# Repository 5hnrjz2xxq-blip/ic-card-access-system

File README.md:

# IC卡门禁系统设计

数字信号处理课程 · 电子系统设计实训

## 项目简介

基于单片机的 IC 卡门禁系统课设：读卡 → 鉴权 → 控门 → 提示/记录；  
门边**旁置演示**（不动家里原锁），并扩展 **Home App 开锁** 与 **手机 NFC 自动化开锁**。

## 技术选型（方案 A 已定稿）

| 模块 | 方案 |
|------|------|
| 主控 | **ESP32-WROOM-32E**（自制 PCB 模组上板） |
| 读卡 | **MFRC522** 实体 Mifare 卡 + **PN532** 读手机 NFC |
| 显示 | OLED I2C（SSD1306） |
| 执行 | 继电器模拟门锁（旁置，不接原锁） |
| 供电 | Type-C 充电 + 3.7V 锂电 + 3.3V LDO |
| 无线 | WiFi + BLE（模组自带） |
| HomeKit | 软件 HAP，家庭 App 门锁开锁（**非** MFi Home Key） |
| iPhone | Home App 开锁 + 碰墙贴 NFC → **快捷指令**开锁 |
| 安卓 / 鸿蒙 | **手机当 IC 卡被 PN532 直接刷开**（HCE），**不是**碰贴触发命令 |
| 开发环境 | VS Code + PlatformIO（**macOS** 编译烧录监视均可用） |
| 代码托管 | GitHub Public |

不用作 HomeKit 主控：正点原子 ATK-T5（涂鸦生态）。

### 开锁通道一览

| 通道 | 说明 |
|------|------|
| 实体 IC 卡 | MFRC522 白名单（课设基础/提高） |
| iPhone · Home App | 软件 HomeKit 门锁 |
| iPhone · NFC | 碰墙贴 → 快捷指令（**非**原生 Home Key） |
| 安卓 / 鸿蒙 · NFC | **手机模拟卡 → PN532 直读开锁**（如刷 IC 卡） |
| 原生 Apple Home Key | **超范围**，需 MFi，课设不做 |

详细需求见 [`docs/需求说明.md`](docs/需求说明.md)，物料见 [`docs/元器件清单.md`](docs/元器件清单.md)。

交互方案应用（手机可打开）：[`index.html`](index.html)

## 开发环境（Windows / Mac）

本仓库在 **Windows 与 Mac** 之间切换开发，工具链统一为 VS Code + PlatformIO。

### 通用步骤

1. 安装 [VS Code](https://code.visualstudio.com/) 与 PlatformIO 插件
2. 安装并登录 GitHub CLI：`gh auth login`（协议选 HTTPS）
3. 同步代码：

```bash
git clone <本仓库地址>
cd <仓库目录>
```

4. 编译：

```bash
pio run
```

5. 烧录 / 监视（端口因机器而异，勿写死进仓库）：

```bash
pio run -t upload
pio device monitor
```

### 协作约定

- 开工先 `git pull`
- 改完 `commit` 后 `push`
- `upload_port` / `monitor_port` 各机器本地处理，不提交
- 仓库默认 **Public**

### 端口差异

| 系统 | 串口示例 |
|------|----------|
| Windows | `COM3` |
| macOS | `/dev/cu.usbmodem*` / `/dev/cu.usbserial*` |

## 目录结构

```text
├── README.md
├── index.html        # 方案 A 交互应用（手机预览）
├── platformio.ini    # PlatformIO 工程配置
├── .gitignore
├── .gitattributes
├── src/              # 固件源码（PlatformIO）
├── include/          # 头文件
├── docs/             # 需求、BOM、计划、原理图说明
├── hardware/         # 原理图 / PCB（KiCad、Gerber、DRC）
├── fab/              # 打样生产文件（Gerber / BOM / 坐标）
└── assets/           # 文档配图
```

## 开发进度

| 阶段 | 内容 | 状态 |
|------|------|------|
| 0 | 环境与仓库 | 进行中 |
| 1 | 需求与方案（方案 A + BOM） | **完成** |
| 2 | 读卡模块联调 | 未开始 |
| 3 | 白名单鉴权与控门 | 未开始 |
| 4 | 管理与记录 | 未开始 |
| 5 | HomeKit / NFC 自动化 | 未开始 |
| 6 | 文档与答辩 | 未开始 |

## 组员

（待补充）

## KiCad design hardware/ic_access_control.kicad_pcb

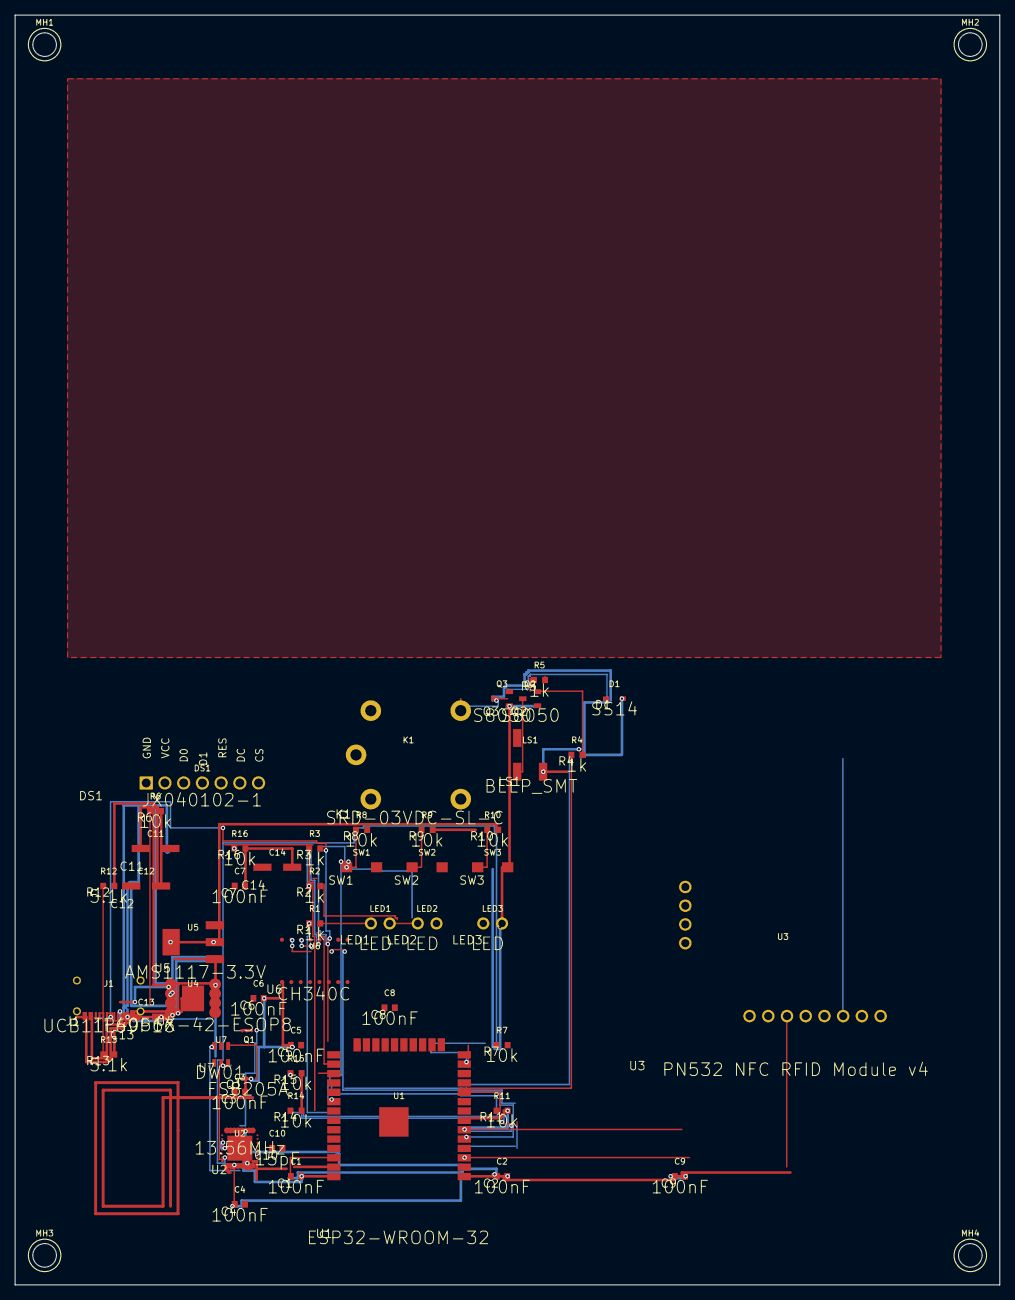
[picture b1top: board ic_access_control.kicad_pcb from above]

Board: 2 copper layers, 133.5 x 172.2 mm, 55 parts (0 on the bottom side), 44 nets.

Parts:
C1, C2, C3, C4, C5, C6, C7, C8, C9, C10: C0603
C11, C12, C13, C14: CAP-SMD_BD4.0-L4.3-W4.3-LS5.3-FD
D1: SOD-323_L1.7-W1.3-LS2.6-RD-1
DS1: OLED-TH_JX040101-1
J1: TYPE-C-SMD_16P-UCB11L69P16
K1: RELAY-TH_SRD-XXVDC-XL-C
LED1, LED2, LED3: LED-TH_BD4.0-P2.54-FD_RED
LS1: BUZ-SMD_3P-L5.2-W5.2-P3.50-BR
MH1, MH2, MH3, MH4: MountingHole_3.2mm_M3
Q1: TSSOP-8_L4.4-W3.0-P0.65-LS6.4-BL-2
Q2, Q3: SOT-23-3_L2.9-W1.3-P1.90-LS2.4-BR
R1, R2, R3, R4, R5, R6, R7, R8, R9, R10, R11, R12, R13, R14, R15, R16: R0603
SW1, SW2, SW3: SW-SMD_L4.0-W2.9-LS5.0
U1: WIFIM-SMD_ESP-WROOM-32
U2: QFN-32_L5.0-W5.0-P0.50-BL-EP3.4
U3: COMM-TH_L42.7-W40.4_PN532_NFC_RFID
U4: SOP-8_L4.9-W3.9-P1.27-LS6.0-TL-EP
U5: SOT-223-3_L6.5-W3.4-P2.30-LS7.0-BR
U6: SOP-16_L10.0-W3.9-P1.27-LS6.0-BL
U7: SOT-23-6_L2.9-W1.6-P0.95-LS2.8-BL

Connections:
+3V3: C2.1, C3.1, C5.1, C8.1, C9.1, C13.1, C14.1, D1.2, K1.1, LS1.1, R7.2, R8.2, R9.2, R10.2, R11.2, R14.2, R15.2, U1.2, U2.6, U2.16, U2.17, U2.19, U3.1, U5.2, U5.4, U6.16
ANT1: C10.2, U2.5, U2.8
ANT_RX: C10.1, U2.23
BAT_GND: Q1.1, Q1.2, Q1.3, U7.6
BOOT: R11.1, U1.25
BUZ: R4.1, U1.10
BUZ_C: LS1.2, Q2.3
CC1: J1.A5, R12.1
CC2: J1.B5, R13.1
CH_V3: C7.1, U6.4
EN: C1.1, R7.1, U1.3
GND: C1.2, C2.2, C3.2, C4.2, C5.2, C6.2, C7.2, C8.2, C9.2, C11.2, C12.2, C13.2, C14.2, J1.1, J1.A1, J1.A12, J1.B1, J1.B12, LED1.2, LED2.2, LED3.2, Q1.6, Q1.7, Q1.8, Q2.2, Q3.2, R6.2, R12.2, R13.2, R16.2, SW1.2, SW2.2, SW3.2, U1.1, U1.15, U1.38, U1.39, U2.7, U2.18, U2.22, U2.30, U2.32, U2.33, U3.2, U3.10, U4.3, U4.9, U5.1, U6.1
LED_G: R1.1, U1.11
LED_R: R2.1, U1.12
LED_S: R3.1, U1.8
NLED1: LED1.1, R1.2
NLED2: LED2.1, R2.2
NLED3: LED3.1, R3.2
NQB2: Q2.1, R4.2
NQB3: Q3.1, R5.2
OC: Q1.5, U7.3
OD: Q1.4, U7.1
PN_SS: U1.23, U3.6
PROG: R6.1, U4.2
RC_RST: U1.13, U2.25
RC_SS: U1.29, U2.29
RLY: R5.1, U1.28
RLY_C: D1.1, K1.2, Q3.3
SCL: R15.1, U1.36, U3.12
SDA: R14.1, U1.33, U3.11
SPI_MISO: U1.31, U2.26, U3.4
SPI_MOSI: U1.37, U2.27, U3.3
SPI_SCK: U1.30, U2.28, U3.5
SW1: R8.1, SW1.1, U1.9
SW2: R9.1, SW2.1, U1.26
SW3: R10.1, SW3.1, U1.16
TEMP: R16.1, U4.1
UART_RX: U1.34, U6.3
UART_TX: U1.35, U6.2
USB_DN: J1.A7, J1.B7, U6.6
USB_DP: J1.A6, J1.B6, U6.5
VBAT: C12.1, U4.5, U5.3, U7.5
VBUS: C6.1, C11.1, J1.A4, J1.A9, J1.B4, J1.B9, U4.4
VMID: C4.1, U2.24

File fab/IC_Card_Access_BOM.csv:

No.	Quantity	Comment	Designator	Footprint	Value	Manufacturer Part	Manufacturer	Supplier Part	Supplier
1	9	100nF	C1,C2,C3,C4,C5,C6,C7,C8,C9	C0603	100nF	ST18B104K500CT	Walsin(华新科)	C2918557	LCSC
2	1	15pF	C10	C0603	15pF	ST18B104K500CT	Walsin(华新科)		LCSC
3	4	CAP-SMD 4*5 10uF ±10% 16V	C11,C12,C13,C14	CAP-SMD_BD4.0-L4.3-W4.3-LS5.3-FD	10uF	CAP-SMD 4*5 10uF ±10% 16V		C9900020910	LCSC
4	1	SS14	D1	SOD-323_L1.7-W1.3-LS2.6-RD-1		SS14		C9900013398	LCSC
5	1	JX040102-1	DS1	OLED-TH_JX040101-1		JX040102-1	技小新	C284855	LCSC
6	1	UCB11L69P16	J1	TYPE-C-SMD_16P-UCB11L69P16		UCB11L69P16		C9900009190	LCSC
7	1	SRD-03VDC-SL-C	K1	RELAY-TH_SRD-XXVDC-XL-C		SRD-03VDC-SL-C	松乐	C24585	LCSC
8	3	LED	LED1,LED2,LED3	LED-TH_BD4.0-P2.54-FD_RED		LED		C9900015665	LCSC
9	1	BEEP_SMT	LS1	BUZ-SMD_3P-L5.2-W5.2-P3.50-BR		BEEP_SMT		C9900006792	LCSC
10	1	FS8205A	Q1	TSSOP-8_L4.4-W3.0-P0.65-LS6.4-BL-2		FS8205A		C14212	LCSC
11	2	S8050	Q2,Q3	SOT-23-3_L2.9-W1.3-P1.90-LS2.4-BR		S8050	Doeshare(德芯)	C2931719	LCSC
12	5	1k	R1,R2,R3,R4,R5	R0603	1k				
13	9	10k	R6,R7,R8,R9,R10,R11,R14,R15,R16	R0603	10k				
14	2	5.1k	R12,R13	R0603	5.1k	RMC06035.1K1%N	Tyohm(幸亚电阻)		LCSC
15	3	轻触按键3*4*H	SW1,SW2,SW3	SW-SMD_L4.0-W2.9-LS5.0		轻触按键3*4*H		C9900017573	LCSC
16	1	ESP32-WROOM-32	U1	WIFIM-SMD_ESP-WROOM-32		ESP32-WROOM-32		C95209	LCSC
17	1	13.56MHz	U2	QFN-32_L5.0-W5.0-P0.50-BL-EP3.4	13.56MHz	MFRC52202HN1,151	NXP(恩智浦)	C11322	LCSC
18	1	PN532 NFC RFID Module v4	U3	COMM-TH_L42.7-W40.4_PN532_NFC_RFID		PN532 NFC RFID Module v4		C9900233104	LCSC
19	1	TP4056X-42-ESOP8	U4	SOP-8_L4.9-W3.9-P1.27-LS6.0-TL-EP		TP4056X-42-ESOP8	TOPPOWER(南京拓微)	C2763448	LCSC
20	1	AMS1117-3.3V	U5	SOT-223-3_L6.5-W3.4-P2.30-LS7.0-BR		AMS1117-3.3V	JSMSEMI(杰盛微)	C5205141	LCSC
21	1	CH340C	U6	SOP-16_L10.0-W3.9-P1.27-LS6.0-BL		CH340C	WCH(南京沁恒)	C84681	LCSC
22	1	DW01	U7	SOT-23-6_L2.9-W1.6-P0.95-LS2.8-BL		DW01	Slkor(萨科微)	C359989	LCSC

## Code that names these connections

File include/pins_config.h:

#pragma once

#include <Arduino.h>

// ==========================================
// IC 卡门禁系统 · 硬件引脚分配
// 对齐 docs/PCB原理图连线规格.md
// ==========================================

// SPI 总线（MFRC522 与 PN532 共用）
constexpr int8_t PIN_SPI_SCK  = 18;
constexpr int8_t PIN_SPI_MISO = 19;
constexpr int8_t PIN_SPI_MOSI = 23;

// MFRC522 (实体 Mifare 卡读头)
constexpr int8_t PIN_RC_SS    = 5;
constexpr int8_t PIN_RC_RST   = 14;

// PN532 (手机 HCE 虚拟卡读头)
constexpr int8_t PIN_PN_SS    = 15;

// I2C 总线 (0.96" OLED SSD1306)
constexpr int8_t PIN_I2C_SDA  = 21;
constexpr int8_t PIN_I2C_SCL  = 22;
constexpr uint8_t OLED_I2C_ADDR = 0x3C;

// 声光交互
constexpr int8_t PIN_BUZZER   = 25;  // Q2 驱动高电平鸣响
constexpr int8_t PIN_LED_G    = 26;  // 绿色 LED：通过
constexpr int8_t PIN_LED_R    = 27;  // 红色 LED：拒绝/报警
constexpr int8_t PIN_LED_S    = 32;  // 蓝色/状态 LED

// 门锁执行机构
constexpr int8_t PIN_RELAY    = 17;  // Q3 驱动高电平吸合
constexpr int8_t PIN_SERVO    = 16;  // 舵机 PWM 信号线 (SG90 橙线)
constexpr int    SERVO_LOCKED_ANGLE   = 0;   // 闭锁角度
constexpr int    SERVO_UNLOCKED_ANGLE = 90;  // 开锁角度

// 人机按键（按下接地，内部/外部上拉）
constexpr int8_t PIN_SW_ADMIN = 33;  // SW1 管理模式
constexpr int8_t PIN_SW_ADD   = 4;   // SW2 录入白名单
constexpr int8_t PIN_SW_DEL   = 13;  // SW3 删除/确认

// 时间参数配置（毫秒）
constexpr uint32_t DOOR_UNLOCK_DURATION_MS = 3000; // 开门持续 3 秒后自动闭锁
constexpr uint32_t CARD_REPEAT_INTERVAL_MS = 2500; // 同一张卡刷卡防重读间隔 2.5 秒
constexpr size_t   MAX_WHITELIST_CAPACITY  = 30;   // 白名单最大容量
constexpr size_t   MAX_ACCESS_LOG_COUNT    = 20;   // 进出记录环形缓冲区大小
